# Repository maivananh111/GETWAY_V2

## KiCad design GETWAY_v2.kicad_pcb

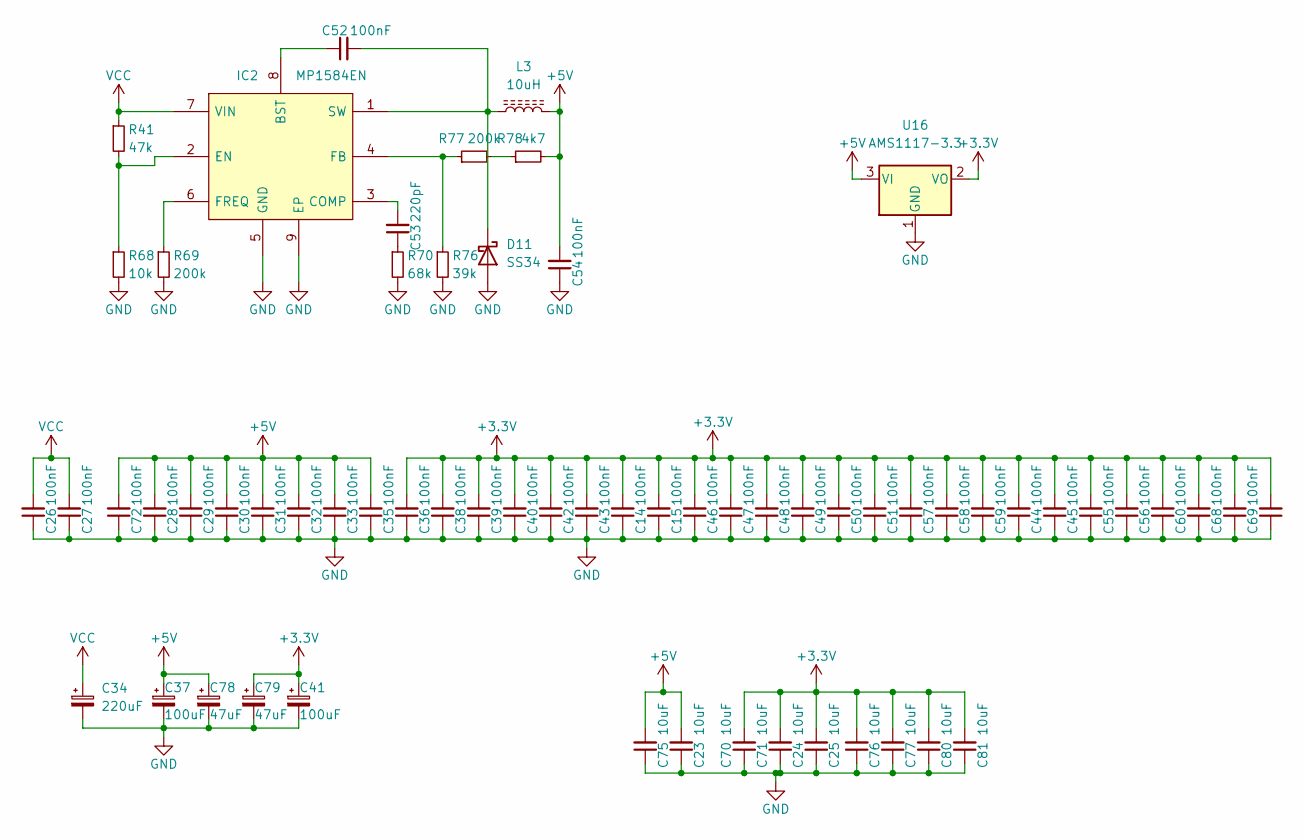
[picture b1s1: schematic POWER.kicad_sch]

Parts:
C14, C15, C26, C27, C28, C29, C30, C31, C32, C33, C35, C36, C38, C39, C40, C42, C43, C44, C45, C46, C47, C48, C49, C50, C51, C52, C54, C55, C56, C57, C58, C59, C60, C68, C69, C72: 100nF; C_0603_1608Metric
C23, C24, C25, C70, C71, C75, C76, C77, C80, C81: 10uF; C_1206_3216Metric
C34: 220uF; CP_Elec_8x10.5
C37, C41: 100uF; CP_Elec_6.3x5.4
C53: 220pF; C_0603_1608Metric
C78, C79: 47uF; CP_Elec_5x5.4
D11: SS34; D_SMA
IC2: MP1584EN; SOIC-8-1EP_3.9x4.9mm_P1.27mm_EP2.514x3.2mm_ThermalVias
L3: 10uH; L_Abracon_ASPI-0630LR
R41: 47k; R_0603_1608Metric
R68: 10k; R_0603_1608Metric
R69, R77: 200k; R_0603_1608Metric
R70: 68k; R_0603_1608Metric
R76: 39k; R_0603_1608Metric
R78: 4k7; R_0603_1608Metric
U16: AMS1117-3.3; SOT-223-3_TabPin2

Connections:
+3.3V: C14.2, C15.2, C24.2, C25.2, C36.2, C38.2, C39.2, C40.2, C41.1, C42.2, C43.2, C44.2, C45.2, C46.2, C47.2, C48.2, C49.2, C50.2, C51.2, C55.2, C56.2, C57.2, C58.2, C59.2, C60.2, C68.2, C69.2, C70.2, C71.2, C76.2, C77.2, C79.1, C80.2, C81.2, U16.2 (VO); also elsewhere on the board
+5V: C23.2, C28.2, C29.2, C30.2, C31.2, C32.2, C33.2, C35.2, C37.1, C54.2, C72.2, C75.2, C78.1, L3.2, R78.2, U16.3 (VI); also elsewhere on the board
GND: C14.1, C15.1, C23.1, C24.1, C25.1, C26.1, C27.1, C28.1, C29.1, C30.1, C31.1, C32.1, C33.1, C34.2, C35.1, C36.1, C37.2, C38.1, C39.1, C40.1, C41.2, C42.1, C43.1, C44.1, C45.1, C46.1, C47.1, C48.1, C49.1, C50.1, C51.1, C54.1, C55.1, C56.1, C57.1, C58.1, C59.1, C60.1, C68.1, C69.1, C70.1, C71.1, C72.1, C75.1, C76.1, C77.1, C78.2, C79.2, C80.1, C81.1, D11.2 (A), IC2.5 (GND), IC2.9 (EP), R68.2, R69.2, R70.2, R76.2, U16.1 (GND); also elsewhere on the board
unnamed: C52.1, IC2.8 (BST)
unnamed: C52.2, D11.1 (K), IC2.1 (SW), L3.1
unnamed: C53.1, R70.1
unnamed: C53.2, IC2.3 (COMP)
unnamed: IC2.2 (EN), R41.2, R68.1
unnamed: IC2.4 (FB), R76.1, R77.1
unnamed: IC2.6 (FREQ), R69.1
unnamed: R77.2, R78.1
VCC: C26.2, C27.2, C34.1, IC2.7 (VIN), R41.1; also elsewhere on the board

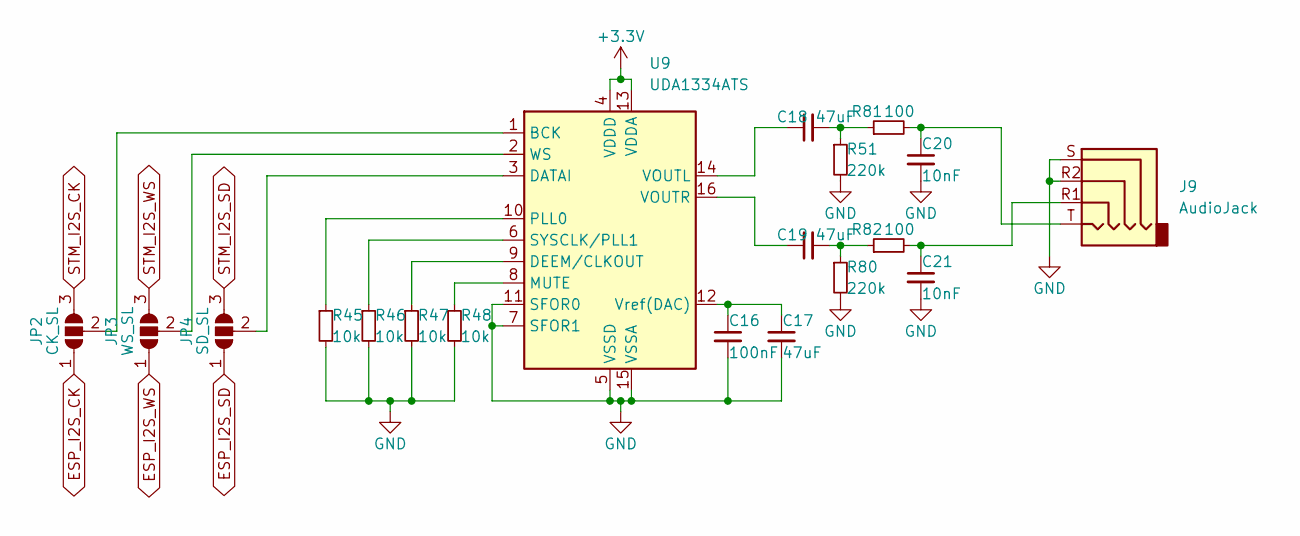
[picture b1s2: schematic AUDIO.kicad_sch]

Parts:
C16: 100nF; C_0603_1608Metric
C17, C18, C19: 47uF; C_1206_3216Metric
C20, C21: 10nF; C_0603_1608Metric
J9: AudioJack; Jack_3.5mm_PJ320D_Horizontal
JP2: CK_SL; SolderJumper-3_P1.3mm_Open_RoundedPad1.0x1.5mm
JP3: WS_SL; SolderJumper-3_P1.3mm_Open_RoundedPad1.0x1.5mm
JP4: SD_SL; SolderJumper-3_P1.3mm_Open_RoundedPad1.0x1.5mm
R45, R46, R47, R48: 10k; R_0603_1608Metric
R51, R80: 220k; R_0603_1608Metric
R81, R82: 100; R_0603_1608Metric
U9: UDA1334ATS; SSOP-16_4.4x5.2mm_P0.65mm

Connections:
+3.3V: U9.4 (VDDD), U9.13 (VDDA); also elsewhere on the board
ESP_I2S_CK: JP2.1 (A); also elsewhere on the board
ESP_I2S_SD: JP4.1 (A); also elsewhere on the board
ESP_I2S_WS: JP3.1 (A); also elsewhere on the board
GND: C16.2, C17.2, C20.2, C21.2, J9.R2, J9.S, R45.2, R46.2, R47.2, R48.2, R51.2, R80.2, U9.5 (VSSD), U9.7 (SFOR1), U9.11 (SFOR0), U9.15 (VSSA); also elsewhere on the board
unnamed: C16.1, C17.1, U9.12 (Vref(DAC))
unnamed: C18.1, U9.14 (VOUTL)
unnamed: C18.2, R51.1, R81.1
unnamed: C19.1, U9.16 (VOUTR)
unnamed: C19.2, R80.1, R82.1
unnamed: C20.1, J9.T, R81.2
unnamed: C21.1, J9.R1, R82.2
unnamed: JP2.2 (C), U9.1 (BCK)
unnamed: JP3.2 (C), U9.2 (WS)
unnamed: JP4.2 (C), U9.3 (DATAI)
unnamed: R45.1, U9.10 (PLL0)
unnamed: R46.1, U9.6 (SYSCLK/PLL1)
unnamed: R47.1, U9.9 (DEEM/CLKOUT)
unnamed: R48.1, U9.8 (MUTE)
STM_I2S_CK: JP2.3 (B); also elsewhere on the board
STM_I2S_SD: JP4.3 (B); also elsewhere on the board
STM_I2S_WS: JP3.3 (B); also elsewhere on the board

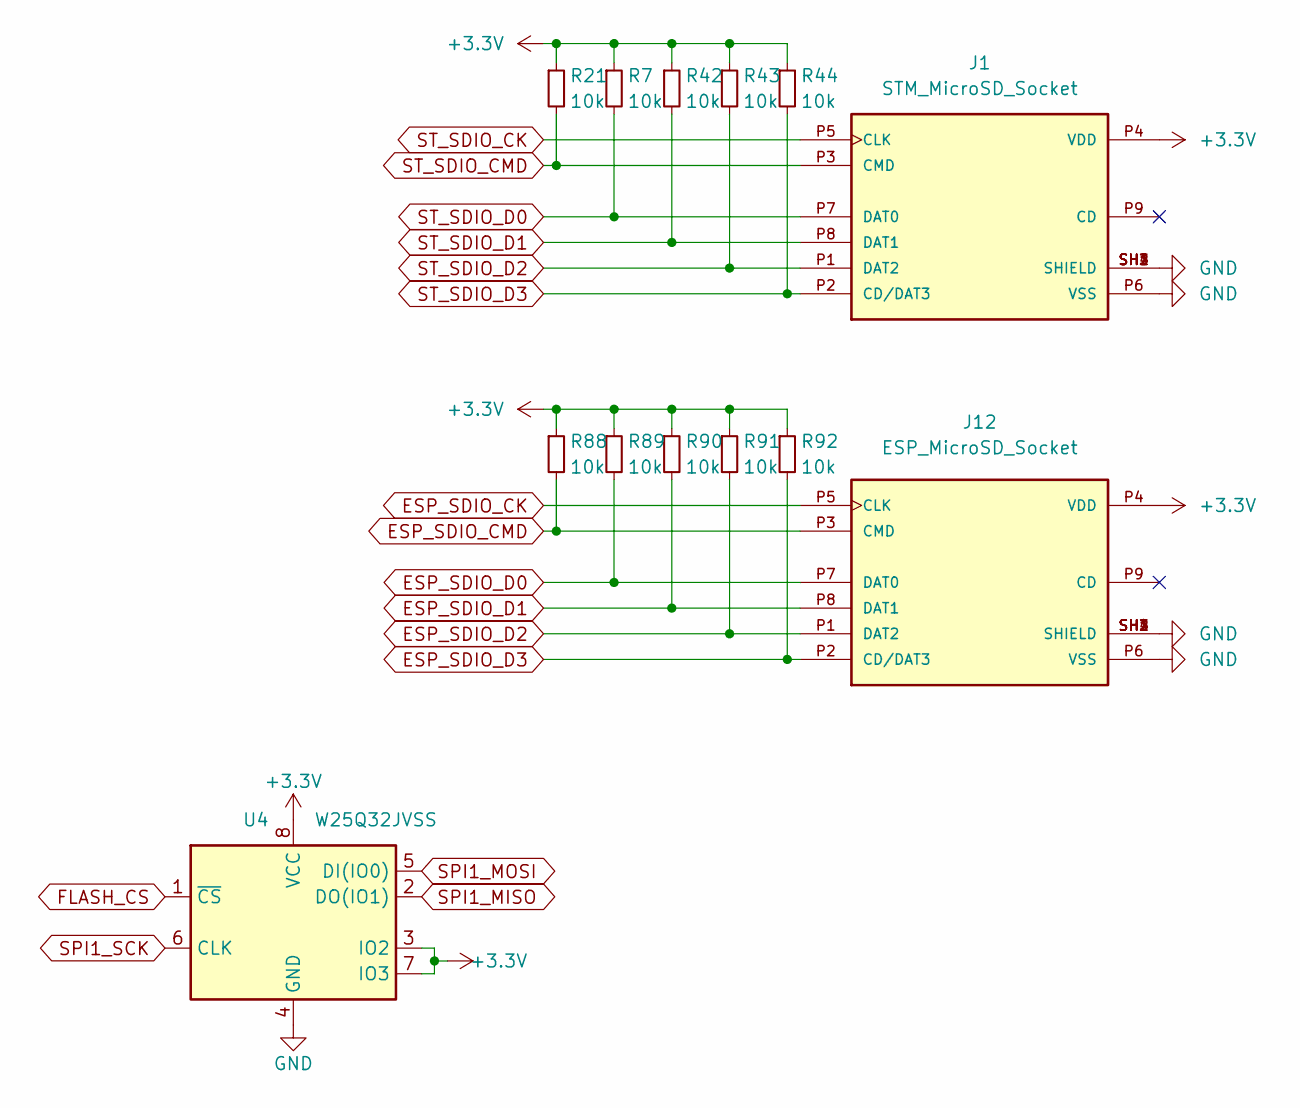
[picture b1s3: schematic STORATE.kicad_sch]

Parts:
J1: STM_MicroSD_Socket; MicroSD_Socket; PARTREV A
J12: ESP_MicroSD_Socket; MicroSD_Socket; PARTREV A
R7, R21, R42, R43, R44, R88, R89, R90, R91, R92: 10k; R_0603_1608Metric
U4: W25Q32JVSS; SOIC-8_5.23x5.23mm_P1.27mm

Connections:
+3.3V: J1.P4 (VDD), J12.P4 (VDD), R7.1, R21.1, R42.1, R43.1, R44.1, R88.1, R89.1, R90.1, R91.1, R92.1, U4.3 (IO2), U4.7 (IO3), U4.8 (VCC); also elsewhere on the board
ESP_SDIO_CK: J12.P5 (CLK); also elsewhere on the board
ESP_SDIO_CMD: J12.P3 (CMD), R88.2; also elsewhere on the board
ESP_SDIO_D0: J12.P7 (DAT0), R89.2; also elsewhere on the board
ESP_SDIO_D1: J12.P8 (DAT1), R90.2; also elsewhere on the board
ESP_SDIO_D2: J12.P1 (DAT2), R91.2; also elsewhere on the board
ESP_SDIO_D3: J12.P2 (CD/DAT3), R92.2; also elsewhere on the board
FLASH_CS: U4.1 (~CS); also elsewhere on the board
GND: J1.P6 (VSS), J1.SH1 (SHIELD), J1.SH2 (SHIELD), J1.SH3 (SHIELD), J1.SH4 (SHIELD), J12.P6 (VSS), J12.SH1 (SHIELD), J12.SH2 (SHIELD), J12.SH3 (SHIELD), J12.SH4 (SHIELD), U4.4 (GND); also elsewhere on the board
SPI1_MISO: U4.2 (DO(IO1)); also elsewhere on the board
SPI1_MOSI: U4.5 (DI(IO0)); also elsewhere on the board
SPI1_SCK: U4.6 (CLK); also elsewhere on the board
ST_SDIO_CK: J1.P5 (CLK); also elsewhere on the board
ST_SDIO_CMD: J1.P3 (CMD), R21.2; also elsewhere on the board
ST_SDIO_D0: J1.P7 (DAT0), R7.2; also elsewhere on the board
ST_SDIO_D1: J1.P8 (DAT1), R42.2; also elsewhere on the board
ST_SDIO_D2: J1.P1 (DAT2), R43.2; also elsewhere on the board
ST_SDIO_D3: J1.P2 (CD/DAT3), R44.2; also elsewhere on the board

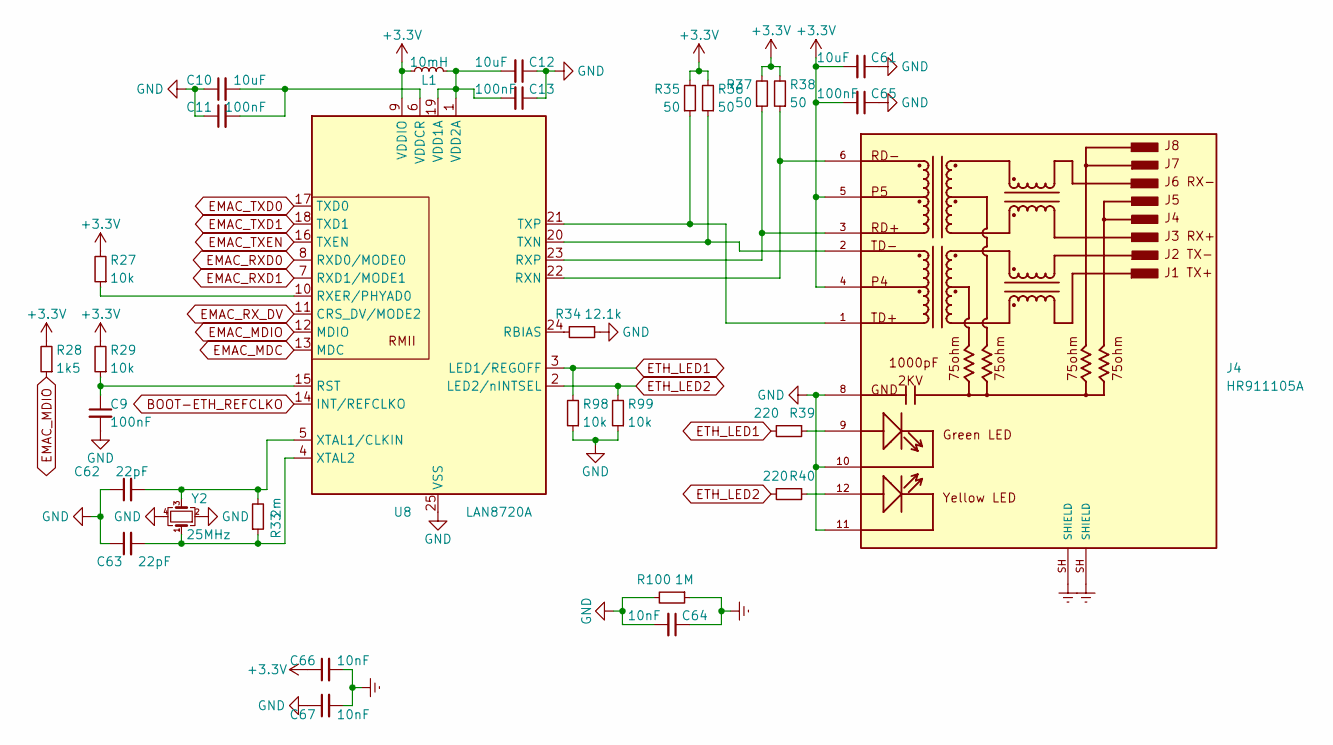
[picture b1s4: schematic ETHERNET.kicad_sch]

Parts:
C9, C11, C13, C65: 100nF; C_0603_1608Metric
C10, C12, C61: 10uF; C_1206_3216Metric
C62, C63: 22pF; C_0603_1608Metric
C64, C66, C67: 10nF; C_1206_3216Metric
J4: HR911105A; HANRUN_RJ45LED_HR911105A; PARTREV A
L1: 10mH; L_1206_3216Metric
R27, R29, R98, R99: 10k; R_0603_1608Metric
R28: 1k5; R_0603_1608Metric
R33: 2m; R_0603_1608Metric
R34: 12.1k; R_0603_1608Metric
R35, R36, R37, R38: 50; R_0603_1608Metric
R39, R40: 220; R_0603_1608Metric
R100: 1M; R_1206_3216Metric
U8: LAN8720A; QFN-24-1EP_4x4mm_P0.5mm_EP2.6x2.6mm
Y2: 25MHz; Crystal_SMD_5032-4Pin_5.0x3.2mm

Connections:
+3.3V: C61.2, C65.2, C66.1, J4.4, J4.5, L1.1, R27.2, R28.2, R29.2, R35.2, R36.2, R37.2, R38.2, U8.9 (VDDIO); also elsewhere on the board
BOOT-ETH_REFCLKO: U8.14 (INT/REFCLKO); also elsewhere on the board
EMAC_MDC: U8.13 (MDC); also elsewhere on the board
EMAC_MDIO: R28.1, U8.12 (MDIO); also elsewhere on the board
EMAC_RXD0: U8.8 (RXD0/MODE0); also elsewhere on the board
EMAC_RXD1: U8.7 (RXD1/MODE1); also elsewhere on the board
EMAC_RX_DV: U8.11 (CRS_DV/MODE2); also elsewhere on the board
EMAC_TXD0: U8.17 (TXD0); also elsewhere on the board
EMAC_TXD1: U8.18 (TXD1); also elsewhere on the board
EMAC_TXEN: U8.16 (TXEN); also elsewhere on the board
ETH_LED1: R39.2, R98.2, U8.3 (LED1/REGOFF)
ETH_LED2: R40.2, R99.2, U8.2 (LED2/nINTSEL)
Earth: C64.1, C66.2, C67.2, J4.SH (SHIELD), R100.1
GND: C9.2, C10.1, C11.1, C12.1, C13.1, C61.1, C62.1, C63.1, C64.2, C65.1, C67.1, J4.8, J4.10, J4.11, R34.1, R98.1, R99.1, R100.2, U8.25 (VSS), Y2.2, Y2.4; also elsewhere on the board
unnamed: C9.1, R29.1, U8.15 (RST)
unnamed: C10.2, C11.2, U8.6 (VDDCR)
unnamed: C12.2, C13.2, L1.2, U8.1 (VDD2A), U8.19 (VDD1A)
unnamed: C62.2, R33.2, U8.5 (XTAL1/CLKIN), Y2.3
unnamed: C63.2, R33.1, U8.4 (XTAL2), Y2.1
unnamed: J4.1, R35.1, U8.21 (TXP)
unnamed: J4.2, R36.1, U8.20 (TXN)
unnamed: J4.3, R37.1, U8.23 (RXP)
unnamed: J4.6, R38.1, U8.22 (RXN)
unnamed: J4.9, R39.1
unnamed: J4.12, R40.1
unnamed: R27.1, U8.10 (RXER/PHYAD0)
unnamed: R34.2, U8.24 (RBIAS)

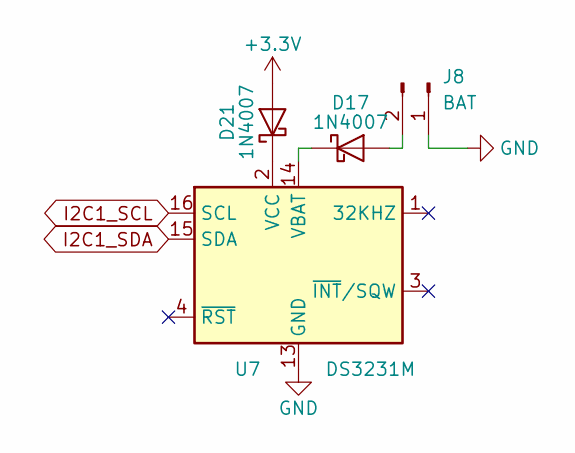
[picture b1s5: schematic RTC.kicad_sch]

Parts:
D17, D21: 1N4007; D_SOD-123F
J8: BAT; XH_2P_2.54mm_Vertical
U7: DS3231M; SOIC-16W_7.5x10.3mm_P1.27mm

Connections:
+3.3V: D21.2 (A); also elsewhere on the board
GND: J8.1, U7.5 (GND), U7.6 (GND), U7.7 (GND), U7.8 (GND), U7.9 (GND), U7.10 (GND), U7.11 (GND), U7.12 (GND), U7.13 (GND); also elsewhere on the board
I2C1_SCL: U7.16 (SCL); also elsewhere on the board
I2C1_SDA: U7.15 (SDA); also elsewhere on the board
unnamed: D17.1 (K), U7.14 (VBAT)
unnamed: D17.2 (A), J8.2
unnamed: D21.1 (K), U7.2 (VCC)

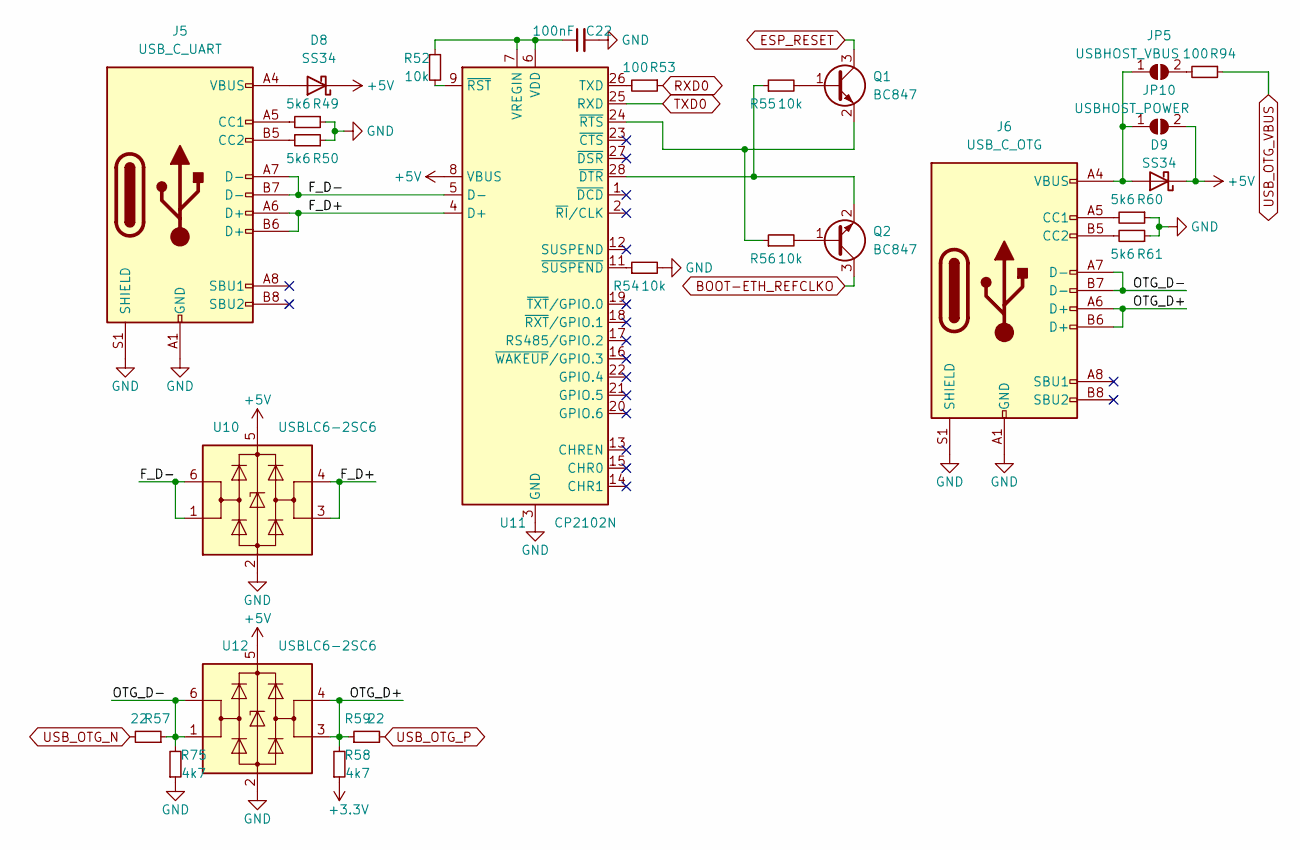
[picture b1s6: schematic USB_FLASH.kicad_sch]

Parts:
C22: 100nF; C_0603_1608Metric
D8, D9: SS34; D_SMA
J5: USB_C_UART; USB_C_Receptacle_HRO_TYPE-C-31-M-12
J6: USB_C_OTG; USB_C_Receptacle_HRO_TYPE-C-31-M-12
JP5: USBHOST_VBUS; SolderJumper-2_P1.3mm_Open_RoundedPad1.0x1.5mm
JP10: USBHOST_POWER; SolderJumper-2_P1.3mm_Open_RoundedPad1.0x1.5mm
Q1, Q2: BC847; SOT-23
R49, R50, R60, R61: 5k6; R_0603_1608Metric
R52, R54, R55, R56: 10k; R_0603_1608Metric
R53, R94: 100; R_0603_1608Metric
R57, R59: 22; R_0603_1608Metric
R58, R75: 4k7; R_0603_1608Metric
U10, U12: USBLC6-2SC6; SOT-23-6
U11: CP2102N; QFN-28-1EP_5x5mm_P0.5mm_EP3.35x3.35mm

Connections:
+3.3V: R58.1; also elsewhere on the board
+5V: D8.1 (K), D9.1 (K), JP10.2 (B), U10.5 (VBUS), U11.8 (VBUS), U12.5 (VBUS); also elsewhere on the board
/USB_FLASH/F_D+: J5.A6 (D+), J5.B6 (D+), U10.3 (I/O2), U10.4 (I/O2), U11.4 (D+)
/USB_FLASH/F_D-: J5.A7 (D-), J5.B7 (D-), U10.1 (I/O1), U10.6 (I/O1), U11.5 (D-)
/USB_FLASH/OTG_D+: J6.A6 (D+), J6.B6 (D+), R58.2, R59.1, U12.3 (I/O2), U12.4 (I/O2)
/USB_FLASH/OTG_D-: J6.A7 (D-), J6.B7 (D-), R57.1, R75.2, U12.1 (I/O1), U12.6 (I/O1)
BOOT-ETH_REFCLKO: Q2.3 (C); also elsewhere on the board
ESP_RESET: Q1.3 (C); also elsewhere on the board
GND: C22.2, J5.A1 (GND), J5.A12 (GND), J5.B1 (GND), J5.B12 (GND), J5.S1 (SHIELD), J6.A1 (GND), J6.A12 (GND), J6.B1 (GND), J6.B12 (GND), J6.S1 (SHIELD), R49.1, R50.1, R54.2, R60.1, R61.1, R75.1, U10.2 (GND), U11.3 (GND), U11.29 (GND), U12.2 (GND); also elsewhere on the board
unnamed: C22.1, R52.1, U11.6 (VDD), U11.7 (VREGIN)
unnamed: D8.2 (A), J5.A4 (VBUS), J5.A9 (VBUS), J5.B4 (VBUS), J5.B9 (VBUS)
unnamed: D9.2 (A), J6.A4 (VBUS), J6.A9 (VBUS), J6.B4 (VBUS), J6.B9 (VBUS), JP5.1 (A), JP10.1 (A)
unnamed: J5.A5 (CC1), R49.2
unnamed: J5.B5 (CC2), R50.2
unnamed: J6.A5 (CC1), R60.2
unnamed: J6.B5 (CC2), R61.2
unnamed: JP5.2 (B), R94.2
unnamed: Q1.1 (B), R55.2
unnamed: Q1.2 (E), R56.1, U11.24 (~RTS)
unnamed: Q2.1 (B), R56.2
unnamed: Q2.2 (E), R55.1, U11.28 (~DTR)
unnamed: R52.2, U11.9 (~RST)
unnamed: R53.2, U11.26 (TXD)
unnamed: R54.1, U11.11 (~SUSPEND)
RXD0: R53.1; also elsewhere on the board
TXD0: U11.25 (RXD); also elsewhere on the board
USB_OTG_N: R57.2; also elsewhere on the board
USB_OTG_P: R59.2; also elsewhere on the board
USB_OTG_VBUS: R94.1; also elsewhere on the board

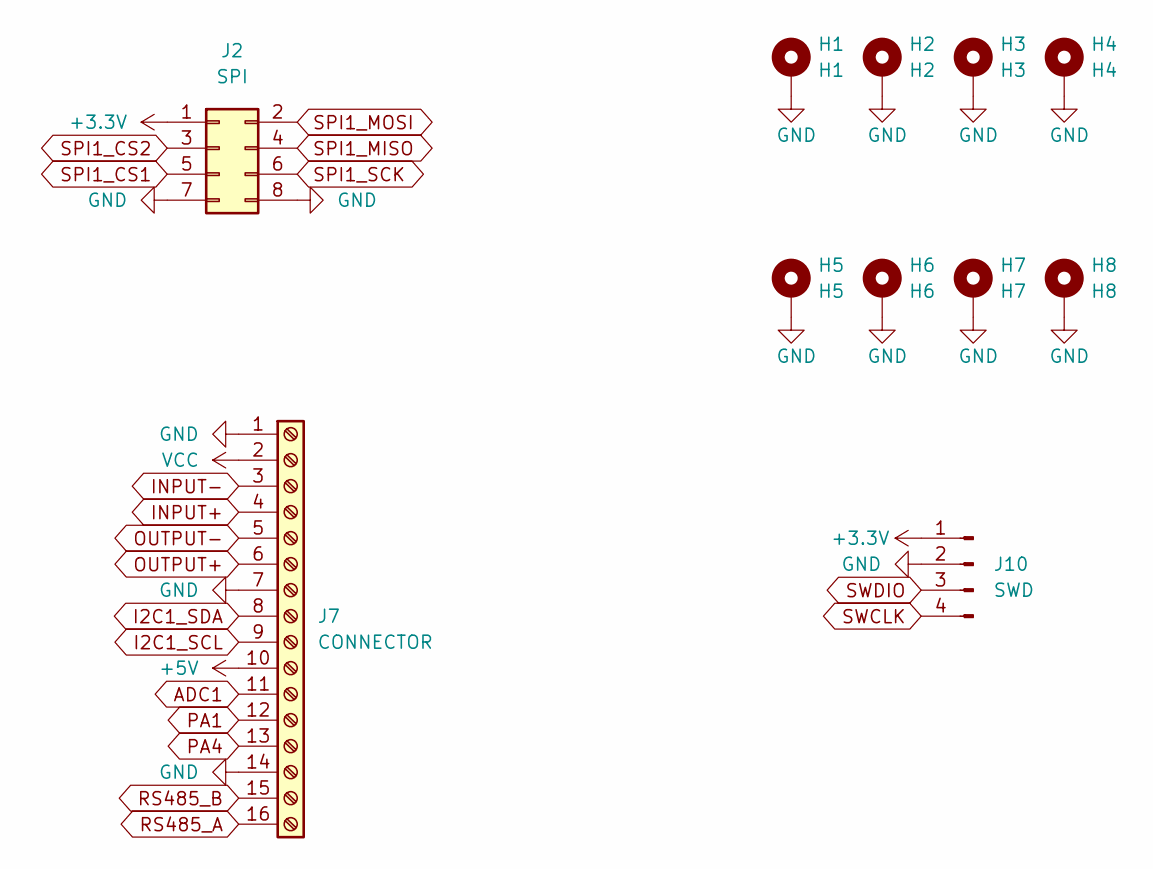
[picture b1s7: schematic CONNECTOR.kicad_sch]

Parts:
H1: H1; MountingHole_2.2mm_M2_Pad_Via
H2: H2; MountingHole_2.2mm_M2_Pad_Via
H3: H3; MountingHole_2.2mm_M2_Pad_Via
H4: H4; MountingHole_2.2mm_M2_Pad_Via
H5: H5; MountingHole_2.2mm_M2_Pad_Via
H6: H6; MountingHole_2.2mm_M2_Pad_Via
H7: H7; MountingHole_2.2mm_M2_Pad_Via
H8: H8; MountingHole_2.2mm_M2_Pad_Via
J2: SPI; PinHeader_2x04_P2.54mm_Vertical
J7: CONNECTOR; TerminalBlock_Phoenix_MKDS-1,5-16-5.08_1x16_P5.08mm_Horizon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
J10: SWD; XH_4P_2.54mm_Horizontal

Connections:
+3.3V: J2.1, J10.1; also elsewhere on the board
+5V: J7.10; also elsewhere on the board
ADC1: J7.11; also elsewhere on the board
GND: H1.1, H2.1, H3.1, H4.1, H5.1, H6.1, H7.1, H8.1, J2.7, J2.8, J7.1, J7.7, J7.14, J10.2; also elsewhere on the board
I2C1_SCL: J7.9; also elsewhere on the board
I2C1_SDA: J7.8; also elsewhere on the board
INPUT+: J7.4; also elsewhere on the board
INPUT-: J7.3; also elsewhere on the board
OUTPUT+: J7.6; also elsewhere on the board
OUTPUT-: J7.5; also elsewhere on the board
PA1: J7.12; also elsewhere on the board
PA4: J7.13; also elsewhere on the board
RS485_A: J7.16; also elsewhere on the board
RS485_B: J7.15; also elsewhere on the board
SPI1_CS1: J2.5; also elsewhere on the board
SPI1_CS2: J2.3; also elsewhere on the board
SPI1_MISO: J2.4; also elsewhere on the board
SPI1_MOSI: J2.2; also elsewhere on the board
SPI1_SCK: J2.6; also elsewhere on the board
SWCLK: J10.4; also elsewhere on the board
SWDIO: J10.3; also elsewhere on the board
VCC: J7.2; also elsewhere on the board

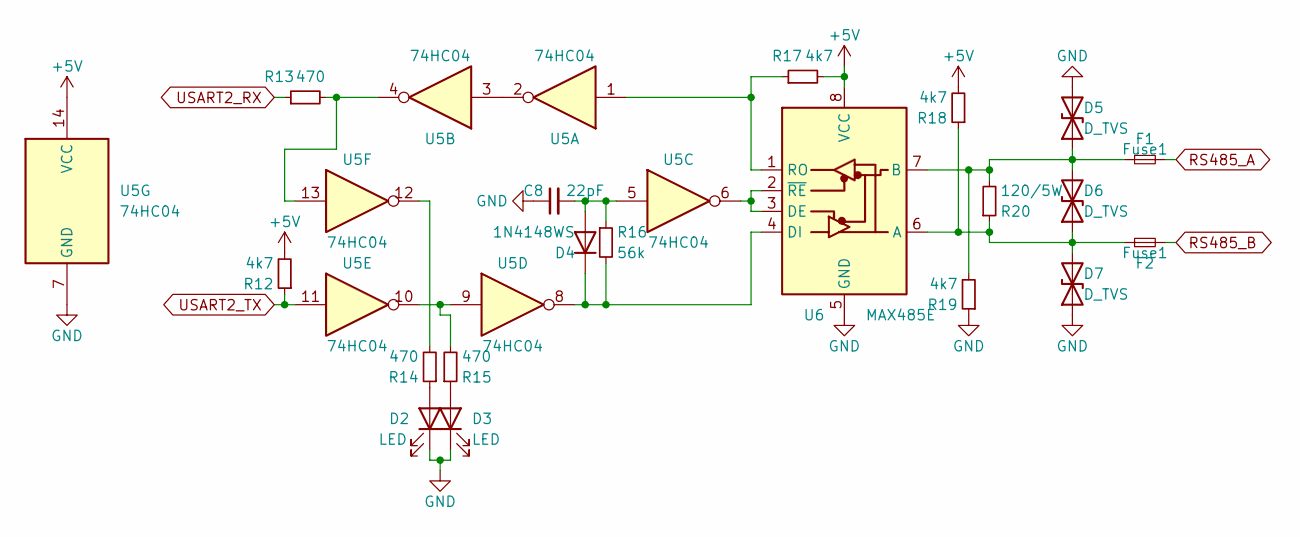
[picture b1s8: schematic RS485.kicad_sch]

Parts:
C8: 22pF; C_0603_1608Metric
D2, D3: LED; LED_0603_1608Metric
D4: 1N4148WS; D_SOD-323
D5, D6, D7: D_TVS; D_SMA
F1, F2: Fuse1; Fuse_2512_6332Metric
R12, R17, R18, R19: 4k7; R_0603_1608Metric
R13, R14, R15: 470; R_0603_1608Metric
R16: 56k; R_0603_1608Metric
R20: 120/5W; R_0805_2012Metric
U5: 74HC04; SOIC-14_3.9x8.7mm_P1.27mm
U6: MAX485E; SOIC-8_3.9x4.9mm_P1.27mm

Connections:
+5V: R12.2, R17.2, R18.2, U5.14 (VCC), U6.8 (VCC); also elsewhere on the board
GND: C8.1, D2.1 (K), D3.1 (K), D5.2 (A2), D7.1 (A1), R19.1, U5.7 (GND), U6.5 (GND); also elsewhere on the board
unnamed: C8.2, D4.2 (A), R16.1, U5.5
unnamed: D2.2 (A), R14.1
unnamed: D3.2 (A), R15.1
unnamed: D4.1 (K), R16.2, U5.8, U6.4 (DI)
unnamed: D5.1 (A1), D6.2 (A2), F1.1, R19.2, R20.2, U6.7 (B)
unnamed: D6.1 (A1), D7.2 (A2), F2.1, R18.1, R20.1, U6.6 (A)
unnamed: R13.2, U5.4, U5.13
unnamed: R14.2, U5.12
unnamed: R15.2, U5.9, U5.10
unnamed: R17.1, U5.1, U6.1 (RO)
unnamed: U5.2, U5.3
unnamed: U5.6, U6.2 (~RE), U6.3 (DE)
RS485_A: F1.2; also elsewhere on the board
RS485_B: F2.2; also elsewhere on the board
USART2_RX: R13.1; also elsewhere on the board
USART2_TX: R12.1, U5.11; also elsewhere on the board

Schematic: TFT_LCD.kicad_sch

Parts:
J3: FPC_32p; FPC_32p_Vertical
R26: 100; R_0603_1608Metric
R31: 100; R_0805_2012Metric

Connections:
+3.3V: J3.3, J3.30, R26.2; also elsewhere on the board
+5V: R31.2; also elsewhere on the board
GND: J3.1, J3.2, J3.31, J3.33 (G1), J3.34 (G2); also elsewhere on the board
I2C2_SCL: J3.6; also elsewhere on the board
I2C2_SDA: J3.7; also elsewhere on the board
LCD_CS: J3.8; also elsewhere on the board
LCD_D0: J3.13; also elsewhere on the board
LCD_D1: J3.14; also elsewhere on the board
LCD_D2: J3.15; also elsewhere on the board
LCD_D3: J3.16; also elsewhere on the board
LCD_D4: J3.17; also elsewhere on the board
LCD_D5: J3.18; also elsewhere on the board
LCD_D6: J3.19; also elsewhere on the board
LCD_D7: J3.20; also elsewhere on the board
LCD_D8: J3.21; also elsewhere on the board
LCD_D9: J3.22; also elsewhere on the board
LCD_D10: J3.23; also elsewhere on the board
LCD_D11: J3.24; also elsewhere on the board
LCD_D12: J3.25; also elsewhere on the board
LCD_D13: J3.26; also elsewhere on the board
LCD_D14: J3.27; also elsewhere on the board
LCD_D15: J3.28; also elsewhere on the board
LCD_LEDC: J3.32; also elsewhere on the board
LCD_RD: J3.12; also elsewhere on the board
LCD_RS: J3.9; also elsewhere on the board
LCD_RST: J3.11; also elsewhere on the board
LCD_WR: J3.10; also elsewhere on the board
unnamed: J3.4, R26.1
unnamed: J3.29, R31.1
TOUCH_INT: J3.5; also elsewhere on the board

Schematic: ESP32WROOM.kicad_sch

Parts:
C6, C7: 100nF; C_0603_1608Metric
D18: LED_RX; LED_0603_1608Metric
D19: LED_TX; LED_0603_1608Metric
J11: ANT2; PinHeader_1x01_P2.54mm_Vertical
J14: ESP_ANTENA; SMA_Amphenol_901-143_Horizontal
R5, R6: 10k; R_0603_1608Metric
R32, R93: 220; R_0603_1608Metric
SW2: ESP RESET; SW_SPST_CK_RS282G05A3
SW3: ESP BOOT; SW_SPST_CK_RS282G05A3
U2: ESP32-WROOM-32U

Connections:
+3.3V: R5.2, R6.2, U2.2 (VDD); also elsewhere on the board
BOOT-ETH_REFCLKO: C7.1, R6.1, SW3.2, U2.25 (IO0); also elsewhere on the board
EMAC_MDC: U2.37 (IO23); also elsewhere on the board
EMAC_MDIO: U2.30 (IO18); also elsewhere on the board
EMAC_RXD0: U2.10 (IO25); also elsewhere on the board
EMAC_RXD1: U2.11 (IO26); also elsewhere on the board
EMAC_RX_DV: U2.12 (IO27); also elsewhere on the board
EMAC_TXD0: U2.31 (IO19); also elsewhere on the board
EMAC_TXD1: U2.36 (IO22); also elsewhere on the board
EMAC_TXEN: U2.33 (IO21); also elsewhere on the board
ESP_I2S_CK: U2.8 (IO32); also elsewhere on the board
ESP_I2S_SD: U2.9 (IO33); also elsewhere on the board
ESP_I2S_WS: U2.29 (IO5); also elsewhere on the board
ESP_RESET: C6.1, R5.1, SW2.2, U2.3 (EN); also elsewhere on the board
ESP_SDIO_CK: U2.13 (IO14); also elsewhere on the board
ESP_SDIO_CMD: U2.23 (IO15); also elsewhere on the board
ESP_SDIO_D0: U2.24 (IO2); also elsewhere on the board
ESP_SDIO_D1: U2.26 (IO4); also elsewhere on the board
ESP_SDIO_D2: U2.14 (IO12); also elsewhere on the board
ESP_SDIO_D3: U2.16 (IO13); also elsewhere on the board
GND: C6.2, C7.2, J14.2 (Ext), R32.1, R93.1, SW2.1, SW3.1, U2.1 (GND), U2.15 (GND), U2.38 (GND), U2.39 (GND); also elsewhere on the board
unnamed: D18.1 (K), R93.2
unnamed: D19.1 (K), R32.2
unnamed: J11.1, J14.1 (In)
RXD0: U2.34 (RXD0/IO3); also elsewhere on the board
TXD0: U2.35 (TXD0/IO1); also elsewhere on the board
USART1_RX: D18.2 (A), U2.28 (IO17); also elsewhere on the board
USART1_TX: D19.2 (A), U2.27 (IO16); also elsewhere on the board

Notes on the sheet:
IO2 - ESP_SDIO_D0
IO12 - ESP_SDIO_D2
IO13 - ESP_SDIO_D3
IO17 - UART2_TX
SDIO
IO19 - EMAC_TX0
IO25 - EMAC_RX0
IO21 - EMAC_TXEN
IO22 - EMAC_TX1
IO26 - EMAC_RX1
ESP-STM
I2S
ESP PROG
IO33 - I2S_SD
IO4 - ESP_SDIO_D1
IO3 - UART0_RX
IO5 - I2S_WS
IO0 - BOOT-EMAC_REFCLKO
IO15 - ESP_SDIO_CMD
ETH
IO27 - EMAC_RX_DV
IO1 - UART0_TX
IO32 - I2S_BCLK
IO14 - ESP_SDIO_CLK
IO16 - UART2_RX
IO18 - EMAC_MDIO
IO23 - EMAC_MDC

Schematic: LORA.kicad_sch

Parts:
J15: LORA_ANTENA; SMA_Amphenol_901-143_Horizontal
J16: ANT1; PinHeader_1x01_P2.54mm_Vertical
U3: Ai-Thinker-Ra-02; Ai-Thinker-Ra-01-LoRa

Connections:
+3.3V: U3.3 (VDD); also elsewhere on the board
GND: J15.2 (Ext), U3.1 (GND), U3.2 (GND), U3.9 (GND), U3.16 (GND); also elsewhere on the board
LORA_CS: U3.15 (~NSS); also elsewhere on the board
LORA_INT: U3.5 (DIO0); also elsewhere on the board
LORA_RST: U3.4 (~RESET); also elsewhere on the board
unnamed: J15.1 (In), J16.1
SPI3_MISO: U3.14 (MOSI); also elsewhere on the board
SPI3_MOSI: U3.13 (MISO); also elsewhere on the board
SPI3_SCK: U3.12 (SCK); also elsewhere on the board

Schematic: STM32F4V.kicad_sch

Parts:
C1, C2, C3: 100nF; C_0603_1608Metric
C4, C5: 22pF; C_0603_1608Metric
D1: LED; LED_0603_1608Metric
JP1: STMBOOT; SolderJumper-3_P1.3mm_Open_RoundedPad1.0x1.5mm
R1: 2m; R_0603_1608Metric
R2, R71, R72, R73, R74: 4k7; R_0603_1608Metric
R3: 10k; R_0603_1608Metric
R4: 220; R_0603_1608Metric
SW1: STMRESET; SW_SPST_CK_RS282G05A3
U1: STM32F407VGTx; LQFP-100_14x14mm_P0.5mm
Y1: 25MHz; Crystal_SMD_5032-4Pin_5.0x3.2mm

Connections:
+3.3V: JP1.3 (B), R3.2, R71.2, R72.2, R73.2, R74.2, U1.11 (VDD), U1.19 (VDD), U1.21 (VREF+), U1.22 (VDDA), U1.28 (VDD), U1.50 (VDD), U1.75 (VDD), U1.100 (VDD); also elsewhere on the board
BUZZER: U1.16 (PC1)
FLASH_CS: U1.98 (PE1); also elsewhere on the board
GND: C1.1, C2.1, C3.1, C4.1, C5.1, JP1.1 (A), R4.1, SW1.2, U1.10 (VSS), U1.20 (VSSA), U1.27 (VSS), U1.74 (VSS), U1.99 (VSS), Y1.2, Y1.4; also elsewhere on the board
I2C1_SCL: R74.1, U1.95 (PB8); also elsewhere on the board
I2C1_SDA: R73.1, U1.96 (PB9); also elsewhere on the board
I2C2_SCL: R72.1, U1.47 (PB10); also elsewhere on the board
I2C2_SDA: R71.1, U1.48 (PB11); also elsewhere on the board
LCD_CS: U1.88 (PD7); also elsewhere on the board
LCD_D0: U1.61 (PD14); also elsewhere on the board
LCD_D1: U1.62 (PD15); also elsewhere on the board
LCD_D2: U1.81 (PD0); also elsewhere on the board
LCD_D3: U1.82 (PD1); also elsewhere on the board
LCD_D4: U1.38 (PE7); also elsewhere on the board
LCD_D5: U1.39 (PE8); also elsewhere on the board
LCD_D6: U1.40 (PE9); also elsewhere on the board
LCD_D7: U1.41 (PE10); also elsewhere on the board
LCD_D8: U1.42 (PE11); also elsewhere on the board
LCD_D9: U1.43 (PE12); also elsewhere on the board
LCD_D10: U1.44 (PE13); also elsewhere on the board
LCD_D11: U1.45 (PE14); also elsewhere on the board
LCD_D12: U1.46 (PE15); also elsewhere on the board
LCD_D13: U1.55 (PD8); also elsewhere on the board
LCD_D14: U1.56 (PD9); also elsewhere on the board
LCD_D15: U1.57 (PD10); also elsewhere on the board
LCD_LEDC: U1.59 (PD12); also elsewhere on the board
LCD_RD: U1.85 (PD4); also elsewhere on the board
LCD_RS: U1.60 (PD13); also elsewhere on the board
LCD_RST: U1.37 (PB2); also elsewhere on the board
LCD_WR: U1.86 (PD5); also elsewhere on the board
LORA_CS: U1.67 (PA8); also elsewhere on the board
LORA_INT: U1.84 (PD3); also elsewhere on the board
LORA_RST: U1.69 (PA10); also elsewhere on the board
unnamed: C1.2, R3.1, SW1.1, U1.14 (NRST)
unnamed: C2.2, U1.49 (VCAP_1)
unnamed: C3.2, U1.73 (VCAP_2)
unnamed: C4.2, R1.2, U1.12 (PH0), Y1.3
unnamed: C5.2, R1.1, U1.13 (PH1), Y1.1
unnamed: D1.1 (K), R4.2
unnamed: JP1.2 (C), R2.1
unnamed: R2.2, U1.94 (BOOT0)
PA0: U1.23 (PA0); also elsewhere on the board
PA1: U1.24 (PA1); also elsewhere on the board
PA4: U1.29 (PA4); also elsewhere on the board
PC0: U1.15 (PC0); also elsewhere on the board
PC13: D1.2 (A), U1.7 (PC13)
PE4: U1.3 (PE4)
PE5: U1.4 (PE5)
PE6: U1.5 (PE6); also elsewhere on the board
SPI1_CS1: U1.1 (PE2); also elsewhere on the board
SPI1_CS2: U1.2 (PE3); also elsewhere on the board
SPI1_MISO: U1.31 (PA6); also elsewhere on the board
SPI1_MOSI: U1.32 (PA7); also elsewhere on the board
SPI1_SCK: U1.30 (PA5); also elsewhere on the board
SPI3_MISO: U1.90 (PB4); also elsewhere on the board
SPI3_MOSI: U1.91 (PB5); also elsewhere on the board
SPI3_SCK: U1.89 (PB3); also elsewhere on the board
STM_I2S_CK: U1.52 (PB13); also elsewhere on the board
STM_I2S_SD: U1.54 (PB15); also elsewhere on the board
STM_I2S_WS: U1.51 (PB12); also elsewhere on the board
ST_SDIO_CK: U1.80 (PC12); also elsewhere on the board
ST_SDIO_CMD: U1.83 (PD2); also elsewhere on the board
ST_SDIO_D0: U1.65 (PC8); also elsewhere on the board
ST_SDIO_D1: U1.66 (PC9); also elsewhere on the board
ST_SDIO_D2: U1.78 (PC10); also elsewhere on the board
ST_SDIO_D3: U1.79 (PC11); also elsewhere on the board
SWCLK: U1.76 (PA14); also elsewhere on the board
SWDIO: U1.72 (PA13); also elsewhere on the board
TOUCH_INT: U1.87 (PD6); also elsewhere on the board
USART1_RX: U1.93 (PB7); also elsewhere on the board
USART1_TX: U1.92 (PB6); also elsewhere on the board
USART2_RX: U1.26 (PA3); also elsewhere on the board
USART2_TX: U1.25 (PA2); also elsewhere on the board
USB_OTG_N: U1.70 (PA11); also elsewhere on the board
USB_OTG_P: U1.71 (PA12); also elsewhere on the board
USB_OTG_VBUS: U1.68 (PA9); also elsewhere on the board

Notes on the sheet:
SDIO_4BIT: CONNECT TO MICROSD CARD.
USART6: CONNECT TO ESP32(Can't use as external pin).
USB: CONNECT TO USB_OTG.
FSMC
LORA
PC13: CONNECT TO LED ON BOARD.
USART2: CONNECT TO RS485(Can't use as external pin).
CAN1: CONNECT TO CAN BUS(Can't use as external pin).
DAC
ADC1
PA9: CONNECT TO LORA CS PIN(Can't use as external pin).
PB2: TFT LCD RESET PIN(Can't connect to external pin).
ESP32
ADC2
SDIO
I2C1: RTC/EXTERNAL I2C.
I2C1
PD12(TIM4_CH1): CONNECT TO LCD LED(Can't use as external pin).
LCD
PE0(EXTI0): CONNECT TO LORA INT PIN(Can't use as external pin).
SPI3: CONNECT TO LORA/FLASH(Can't use as external pin).
SPI1: EXTERNAL SPI.
PE1(EXTI1): CONNECT TO LORA2 INT PIN(Can't use as external pin).
AUDIO
PD6(EXTI6): CONNECT TO TOUCH INT PIN(Can't use as external pin).
I2C2: CONNECT TO TOUCH LCD(Can't use as external pin).
I2S2: CONNECT TO AUDIO.
PC0: CONNECT TO INPUT PIN(Can't use as external pin).
PA10: CONNECT TO LORA RST PIN(Can't use as external pin).
PA8: CONNECT TO LORA2 CS PIN(Can't use as external pin).
INPUT
FSMC: CONNECT TO TFT_LCD(Can't use as external pin).
SPI1
SWD
FLASH
USB_OTG
TOUCH
PA0: CONNECT TO OUTPUT PIN(Can't use as external pin).
PA15: CONNECT TO FLASH CS PIN(Can't use as external pin).
RS485

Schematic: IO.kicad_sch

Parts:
C73, C74: 100nF; C_0603_1608Metric
D13, D16: Z3V3; D_SOD-123F
D15: Z12V; D_SOD-123F
R10, R24, R104, R107: 10k; R_0603_1608Metric
R23, R83: 220; R_0603_1608Metric
R25, R84: 22k; R_0603_1608Metric
R86: 6k8; R_0603_1608Metric
R102: 30k; R_0603_1608Metric
R105: 100; R_0603_1608Metric
U13, U14: LTV-817S; SMDIP-4_W9.53mm
U15: LM358; SOIC-8_3.9x4.9mm_P1.27mm

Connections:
+3.3V: R24.2; also elsewhere on the board
+5V: U15.8 (V+); also elsewhere on the board
ADC1: C73.1, R84.1; also elsewhere on the board
GND: C73.2, C74.2, D15.2 (A), D16.2 (A), R25.1, R86.2, R102.2, R107.2, U13.2, U14.3, U15.4 (V-); also elsewhere on the board
INPUT+: R10.2; also elsewhere on the board
INPUT-: D13.2 (A), U14.2; also elsewhere on the board
unnamed: D13.1 (K), R10.1, R23.2
unnamed: D15.1 (K), R84.2, R86.1, U15.3 (+)
unnamed: R23.1, U14.1
unnamed: R83.1, U13.1
unnamed: R102.1, R104.2, U15.2 (-)
unnamed: R104.1, U15.1, U15.5 (+)
unnamed: R105.2, U15.6 (-), U15.7
OUTPUT+: U13.4; also elsewhere on the board
OUTPUT-: U13.3; also elsewhere on the board
PA0: C74.1, D16.1 (K), R105.1, R107.1; also elsewhere on the board
PC0: R24.1, R25.2, U14.4; also elsewhere on the board
PE6: R83.2; also elsewhere on the board
